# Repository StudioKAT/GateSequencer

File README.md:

# Gate Sequencer

## 概要 / Overview

**Gate Sequencer** は、トグルスイッチ式の多機能ゲートシーケンサーです。   
・独立した2つのクロックで動く **8 Stepシーケンサー x2**  
・パフォーマンス機能を備えた **16 Stepシーケンサー**  
・可変長・経路変更可能な **シフトレジスタ (Turing Machine)**  
の3つの機能を備え、スイッチ一つで切り替えて使用できます。

**Gate Sequencer** is a multi-functional gate sequencer equipped with toggle switches. It features three distinct functions that can be switched via a single mode switch:
* **8-Step Sequencer x2** running on independent clocks.
* **16-Step Sequencer** with performance features.
* **Shift Register (Turing Machine)** with variable length and routing capabilities. 

## 仕様 / Spec
- Format: Eurorack
- Function: Gate Sequencer
- Current needs: +12V: 50mA, -12V: 0mA
- Width: 14 HP
- Depth: 25mm (including power connector)

## 販売 / Sales

StudioKATオフィシャルショップで販売しています。(日本国内限定)  
https://www.studiokat.jp/items/164466252

## ライセンス / License

この作品は [Creative Commons 表示 - 継承 4.0 国際 (CC BY-SA 4.0)](https://creativecommons.org/licenses/by-sa/4.0/deed.ja) の下でライセンスされています。  
This work is licensed under the [Creative Commons Attribution-ShareAlike 4.0 International License](https://creativecommons.org/licenses/by-sa/4.0/).

## クレジット / Credits

- Designed by : StudioKAT
- Website : https://www.studiokat.jp/
- GitHub : https://github.com/StudioKAT
- X(Twitter) : https://x.com/StudioKAT_synth
- Instagram : https://www.instagram.com/studiokat_modular/

## 更新履歴 / Changelog

- `2026-10-29`：v2.0 リリース
- `2025-11-22`：v1.0 リリース

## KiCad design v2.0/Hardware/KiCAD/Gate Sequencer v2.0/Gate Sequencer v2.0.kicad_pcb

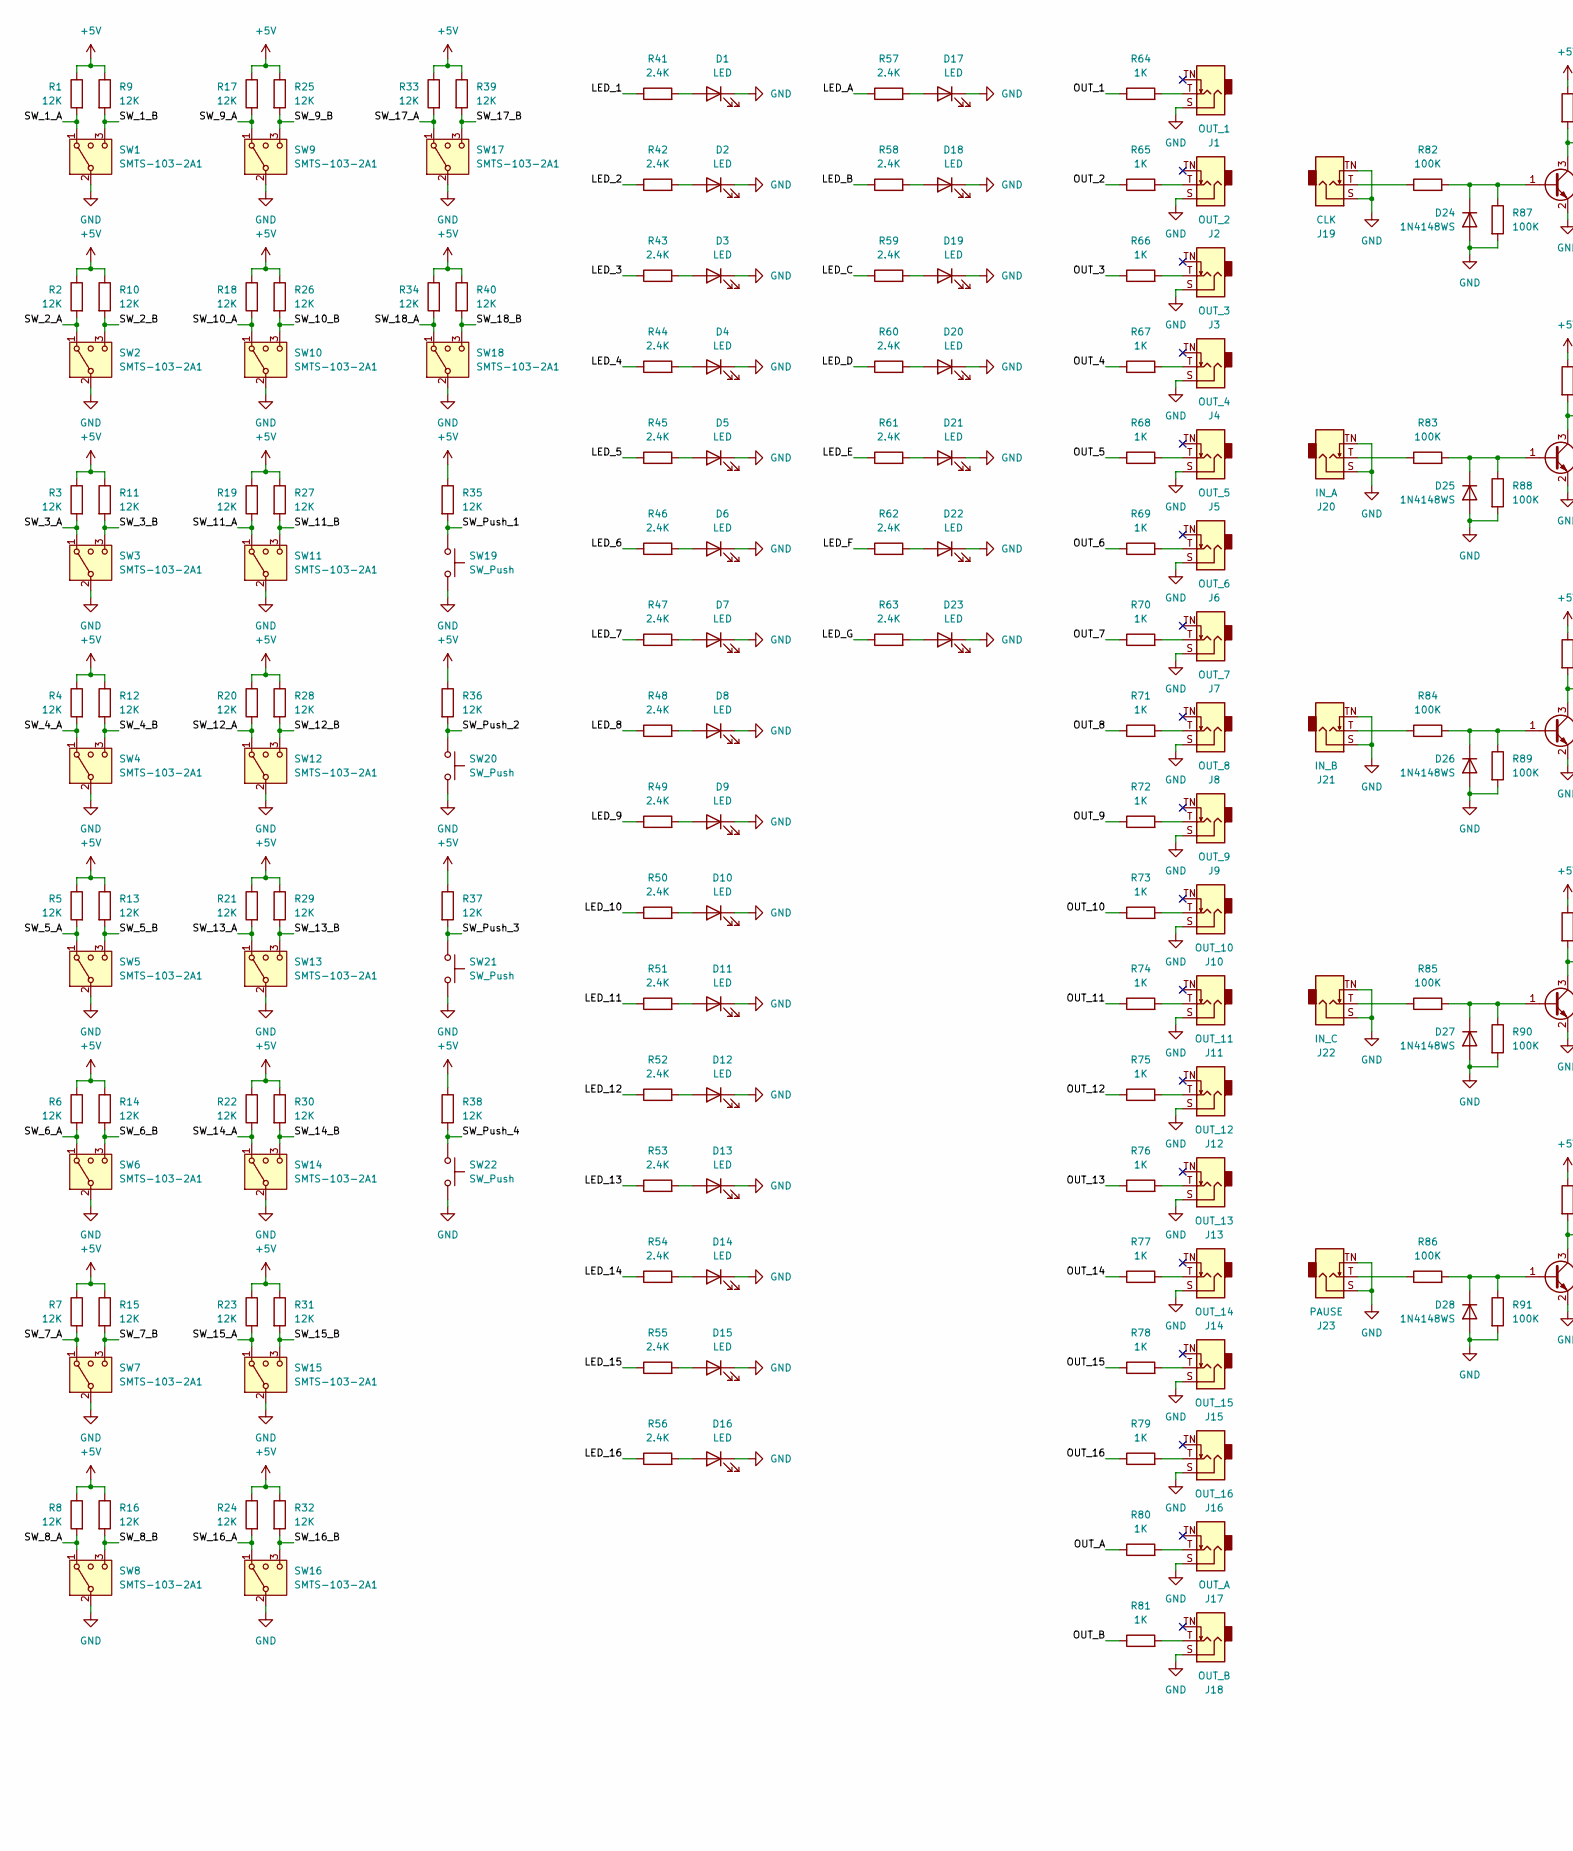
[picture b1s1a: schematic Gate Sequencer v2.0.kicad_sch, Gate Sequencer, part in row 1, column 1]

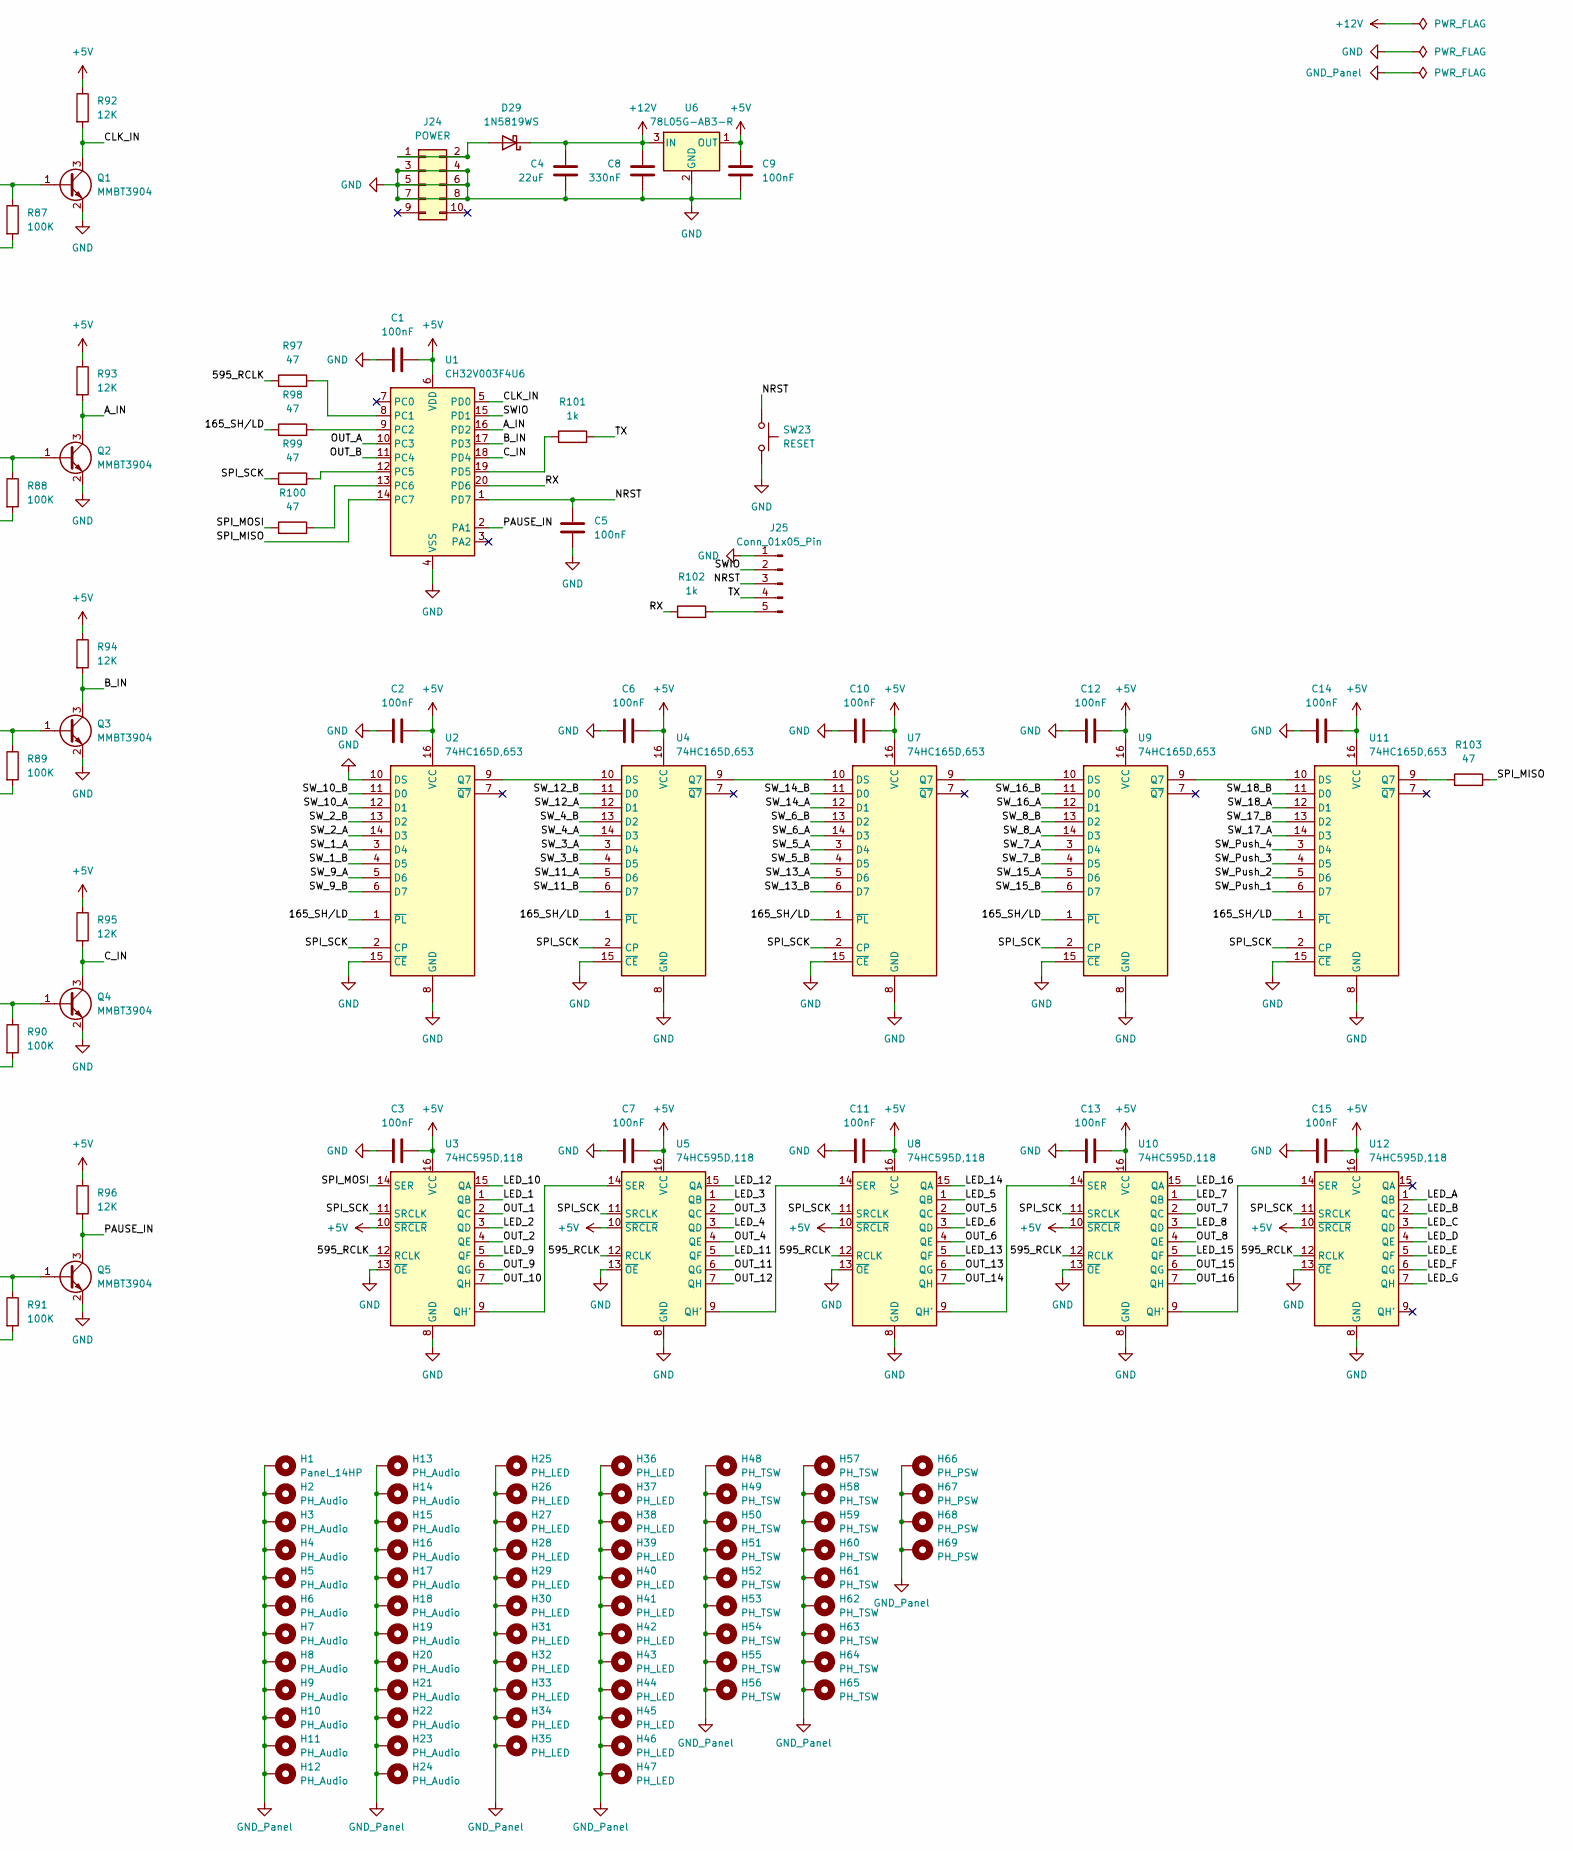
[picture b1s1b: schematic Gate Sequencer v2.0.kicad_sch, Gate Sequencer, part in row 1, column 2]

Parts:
C1, C2, C3, C6, C7, C10, C11, C12, C13, C14, C15: 100nF; C_0603_1608Metric; LCSC C14663
C4: 22uF; C_0805_2012Metric; LCSC C45783
C5, C9: 100nF; C_0603_1608Metric; Voltage 50V; Tolerance ±10%; MFR Part CC0603KRX7R9BB104; JLC Type Basic
C8: 330nF; C_0603_1608Metric; Voltage 25V; Tolerance ±10%; MFR Part 0603B334K250NT; LCSC C1615
D1, D2, D3, D4, D5, D6, D7, D8, D9, D10, D11, D12, D13, D14, D15, D16, D17, D18, D19, D20, D21, D22, D23: LED; LED_D3.0mm_2hp
D24, D25, D26, D27, D28: 1N4148WS; D_SOD-323; LCSC C2128
D29: 1N5819WS; D_SOD-323; LCSC C64886
H1: Panel_14HP
H2, H3, H4, H5, H6, H7, H8, H9, H10, H11, H12, H13, H14, H15, H16, H17, H18, H19, H20, H21, H22, H23, H24: PH_Audio; PH_AudioJack_3.5mm_Pad
H25, H26, H27, H28, H29, H30, H31, H32, H33, H34, H35, H36, H37, H38, H39, H40, H41, H42, H43, H44, H45, H46, H47: PH_LED; PH_LED_3.0mm_Pad
H48, H49, H50, H51, H52, H53, H54, H55, H56, H57, H58, H59, H60, H61, H62, H63, H64, H65: PH_TSW; PH_TactileSwitch_5.5mm_Pad
H66, H67, H68, H69: PH_PSW; PH_ToggleSwitch_5.1mm_Pad
J1: OUT_1; AudioJack_PJ301M-12
J2: OUT_2; AudioJack_PJ301M-12
J3: OUT_3; AudioJack_PJ301M-12
J4: OUT_4; AudioJack_PJ301M-12
J5: OUT_5; AudioJack_PJ301M-12
J6: OUT_6; AudioJack_PJ301M-12
J7: OUT_7; AudioJack_PJ301M-12
J8: OUT_8; AudioJack_PJ301M-12
J9: OUT_9; AudioJack_PJ301M-12
J10: OUT_10; AudioJack_PJ301M-12
J11: OUT_11; AudioJack_PJ301M-12
J12: OUT_12; AudioJack_PJ301M-12
J13: OUT_13; AudioJack_PJ301M-12
J14: OUT_14; AudioJack_PJ301M-12
J15: OUT_15; AudioJack_PJ301M-12
J16: OUT_16; AudioJack_PJ301M-12
J17: OUT_A; AudioJack_PJ301M-12
J18: OUT_B; AudioJack_PJ301M-12
J19: CLK; AudioJack_PJ301M-12
J20: IN_A; AudioJack_PJ301M-12
J21: IN_B; AudioJack_PJ301M-12
J22: IN_C; AudioJack_PJ301M-12
J23: PAUSE; AudioJack_PJ301M-12
J24: POWER; PinHeader_2x05_2.54mm_Europower
J25: Conn_01x05_Pin; PinHeader_1x05_P2.54mm_Vertical
Q1, Q2, Q3, Q4, Q5: MMBT3904; SOT-23; LCSC C20526
R1, R2, R3, R4, R5, R6, R7, R8, R9, R10, R11, R12, R13, R14, R15, R16, R17, R18, R19, R20, R21, R22, R23, R24, R25, R26, R27, R28, R29, R30, R31, R32, R33, R34, R35, R36, R37, R38, R39, R40, R92, R93, R94, R95, R96: 12K; R_0603_1608Metric; LCSC C22790
R41, R42, R43, R44, R45, R46, R47, R48, R49, R50, R51, R52, R53, R54, R55, R56, R57, R58, R59, R60, R61, R62, R63: 2.4K; R_0603_1608Metric; LCSC C22940
R64, R65, R66, R67, R68, R69, R70, R71, R72, R73, R74, R75, R76, R77, R78, R79, R80, R81: 1K; R_0603_1608Metric; LCSC C21190
R82, R83, R84, R85, R86, R87, R88, R89, R90, R91: 100K; R_0603_1608Metric; LCSC C25803
R97, R98, R99, R100, R103: 47; R_0603_1608Metric; Tolerance ±1%; MFR Part 0603WAF470JT5E; JLC Type Basic
R101, R102: 1k; R_0603_1608Metric; Tolerance ±1%; MFR Part 0603WAF1001T5E; JLC Type Basic
SW1, SW2, SW3, SW4, SW5, SW6, SW7, SW8, SW9, SW10, SW11, SW12, SW13, SW14, SW15, SW16, SW17, SW18: SMTS-103-2A1; ToggleSwitch_SMTS-103-2A1
SW19, SW20, SW21, SW22: SW_Push; SW_PUSH_6mm_H13mm
SW23: RESET; SW_Push_TS-1088-AR02016; LCSC C720477
U1: CH32V003F4U6; QFN-20-1EP_3x3mm_P0.4mm_EP1.65x1.65mm; LCSC C5299908
U2, U4, U7, U9, U11: 74HC165D,653; SOIC-16_3.9x9.9mm_P1.27mm; LCSC C5613
U3, U5, U8, U10, U12: 74HC595D,118; SOIC-16_3.9x9.9mm_P1.27mm; LCSC C5947
U6: 78L05G-AB3-R; SOT-89-3; MFR Part 78L05G-AB3-R; JLC Type Basic

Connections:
+5V: C1.2, C2.2, C3.2, C6.2, C7.2, C9.1, C10.2, C11.2, C12.2, C13.2, C14.2, C15.2, R1.1, R2.1, R3.1, R4.1, R5.1, R6.1, R7.1, R8.1, R9.1, R10.1, R11.1, R12.1, R13.1, R14.1, R15.1, R16.1, R17.1, R18.1, R19.1, R20.1, R21.1, R22.1, R23.1, R24.1, R25.1, R26.1, R27.1, R28.1, R29.1, R30.1, R31.1, R32.1, R33.1, R34.1, R35.1, R36.1, R37.1, R38.1, R39.1, R40.1, R92.1, R93.1, R94.1, R95.1, R96.1, U1.6 (VDD), U2.16 (VCC), U3.10 (~SRCLR), U3.16 (VCC), U4.16 (VCC), U5.10 (~SRCLR), U5.16 (VCC), U6.1 (OUT), U7.16 (VCC), U8.10 (~SRCLR), U8.16 (VCC), U9.16 (VCC), U10.10 (~SRCLR), U10.16 (VCC), U11.16 (VCC), U12.10 (~SRCLR), U12.16 (VCC)
+12V: C4.1, C8.1, D29.1 (K), U6.3 (IN)
/165_SH/LD: R98.1, U2.1 (~PL), U4.1 (~PL), U7.1 (~PL), U9.1 (~PL), U11.1 (~PL)
/595_RCLK: R97.1, U3.12 (RCLK), U5.12 (RCLK), U8.12 (RCLK), U10.12 (RCLK), U12.12 (RCLK)
/A_IN: Q2.3 (C), R93.2, U1.16 (PD2)
/B_IN: Q3.3 (C), R94.2, U1.17 (PD3)
/CLK_IN: Q1.3 (C), R92.2, U1.5 (PD0)
/C_IN: Q4.3 (C), R95.2, U1.18 (PD4)
/LED_1: R41.1, U3.1 (QB)
/LED_2: R42.1, U3.3 (QD)
/LED_3: R43.1, U5.1 (QB)
/LED_4: R44.1, U5.3 (QD)
/LED_5: R45.1, U8.1 (QB)
/LED_6: R46.1, U8.3 (QD)
/LED_7: R47.1, U10.1 (QB)
/LED_8: R48.1, U10.3 (QD)
/LED_9: R49.1, U3.5 (QF)
/LED_10: R50.1, U3.15 (QA)
/LED_11: R51.1, U5.5 (QF)
/LED_12: R52.1, U5.15 (QA)
/LED_13: R53.1, U8.5 (QF)
/LED_14: R54.1, U8.15 (QA)
/LED_15: R55.1, U10.5 (QF)
/LED_16: R56.1, U10.15 (QA)
/LED_A: R57.1, U12.1 (QB)
/LED_B: R58.1, U12.2 (QC)
/LED_C: R59.1, U12.3 (QD)
/LED_D: R60.1, U12.4 (QE)
/LED_E: R61.1, U12.5 (QF)
/LED_F: R62.1, U12.6 (QG)
/LED_G: R63.1, U12.7 (QH)
/NRST: C5.1, J25.3, SW23.1, U1.1 (PD7)
/OUT_1: R64.1, U3.2 (QC)
/OUT_2: R65.1, U3.4 (QE)
/OUT_3: R66.1, U5.2 (QC)
/OUT_4: R67.1, U5.4 (QE)
/OUT_5: R68.1, U8.2 (QC)
/OUT_6: R69.1, U8.4 (QE)
/OUT_7: R70.1, U10.2 (QC)
/OUT_8: R71.1, U10.4 (QE)
/OUT_9: R72.1, U3.6 (QG)
/OUT_10: R73.1, U3.7 (QH)
/OUT_11: R74.1, U5.6 (QG)
/OUT_12: R75.1, U5.7 (QH)
/OUT_13: R76.1, U8.6 (QG)
/OUT_14: R77.1, U8.7 (QH)
/OUT_15: R78.1, U10.6 (QG)
/OUT_16: R79.1, U10.7 (QH)
/OUT_A: R80.1, U1.10 (PC3)
/OUT_B: R81.1, U1.11 (PC4)
/PAUSE_IN: Q5.3 (C), R96.2, U1.2 (PA1)
/RX: R102.1, U1.20 (PD6)
/SPI_MISO: R103.2, U1.14 (PC7)
/SPI_MOSI: R100.1, U3.14 (SER)
/SPI_SCK: R99.1, U2.2 (CP), U3.11 (SRCLK), U4.2 (CP), U5.11 (SRCLK), U7.2 (CP), U8.11 (SRCLK), U9.2 (CP), U10.11 (SRCLK), U11.2 (CP), U12.11 (SRCLK)
/SWIO: J25.2, U1.15 (PD1)
/SW_1_A: R1.2, SW1.1, U2.3 (D4)
/SW_1_B: R9.2, SW1.3 (4), U2.4 (D5)
/SW_2_A: R2.2, SW2.1, U2.14 (D3)
/SW_2_B: R10.2, SW2.3 (4), U2.13 (D2)
/SW_3_A: R3.2, SW3.1, U4.3 (D4)
/SW_3_B: R11.2, SW3.3 (4), U4.4 (D5)
/SW_4_A: R4.2, SW4.1, U4.14 (D3)
/SW_4_B: R12.2, SW4.3 (4), U4.13 (D2)
/SW_5_A: R5.2, SW5.1, U7.3 (D4)
/SW_5_B: R13.2, SW5.3 (4), U7.4 (D5)
/SW_6_A: R6.2, SW6.1, U7.14 (D3)
/SW_6_B: R14.2, SW6.3 (4), U7.13 (D2)
/SW_7_A: R7.2, SW7.1, U9.3 (D4)
/SW_7_B: R15.2, SW7.3 (4), U9.4 (D5)
/SW_8_A: R8.2, SW8.1, U9.14 (D3)
/SW_8_B: R16.2, SW8.3 (4), U9.13 (D2)
/SW_9_A: R17.2, SW9.1, U2.5 (D6)
/SW_9_B: R25.2, SW9.3 (4), U2.6 (D7)
/SW_10_A: R18.2, SW10.1, U2.12 (D1)
/SW_10_B: R26.2, SW10.3 (4), U2.11 (D0)
/SW_11_A: R19.2, SW11.1, U4.5 (D6)
/SW_11_B: R27.2, SW11.3 (4), U4.6 (D7)
/SW_12_A: R20.2, SW12.1, U4.12 (D1)
/SW_12_B: R28.2, SW12.3 (4), U4.11 (D0)
/SW_13_A: R21.2, SW13.1, U7.5 (D6)
/SW_13_B: R29.2, SW13.3 (4), U7.6 (D7)
/SW_14_A: R22.2, SW14.1, U7.12 (D1)
/SW_14_B: R30.2, SW14.3 (4), U7.11 (D0)
/SW_15_A: R23.2, SW15.1, U9.5 (D6)
/SW_15_B: R31.2, SW15.3 (4), U9.6 (D7)
/SW_16_A: R24.2, SW16.1, U9.12 (D1)
/SW_16_B: R32.2, SW16.3 (4), U9.11 (D0)
/SW_17_A: R33.2, SW17.1, U11.14 (D3)
/SW_17_B: R39.2, SW17.3 (4), U11.13 (D2)
/SW_18_A: R34.2, SW18.1, U11.12 (D1)
/SW_18_B: R40.2, SW18.3 (4), U11.11 (D0)
/SW_Push_1: R35.2, SW19.1, U11.6 (D7)
/SW_Push_2: R36.2, SW20.1, U11.5 (D6)
/SW_Push_3: R37.2, SW21.1, U11.4 (D5)
/SW_Push_4: R38.2, SW22.1, U11.3 (D4)
/TX: J25.4, R101.2
GND: C1.1, C2.1, C3.1, C4.2, C5.2, C6.1, C7.1, C8.2, C9.2, C10.1, C11.1, C12.1, C13.1, C14.1, C15.1, D1.1 (K), D2.1 (K), D3.1 (K), D4.1 (K), D5.1 (K), D6.1 (K), D7.1 (K), D8.1 (K), D9.1 (K), D10.1 (K), D11.1 (K), D12.1 (K), D13.1 (K), D14.1 (K), D15.1 (K), D16.1 (K), D17.1 (K), D18.1 (K), D19.1 (K), D20.1 (K), D21.1 (K), D22.1 (K), D23.1 (K), D24.2 (A), D25.2 (A), D26.2 (A), D27.2 (A), D28.2 (A), J1.S, J2.S, J3.S, J4.S, J5.S, J6.S, J7.S, J8.S, J9.S, J10.S, J11.S, J12.S, J13.S, J14.S, J15.S, J16.S, J17.S, J18.S, J19.S, J19.TN, J20.S, J20.TN, J21.S, J21.TN, J22.S, J22.TN, J23.S, J23.TN, J24.3, J24.4, J24.5, J24.6, J24.7, J24.8, J25.1, Q1.2 (E), Q2.2 (E), Q3.2 (E), Q4.2 (E), Q5.2 (E), R87.2, R88.2, R89.2, R90.2, R91.2, SW1.2 (3), SW2.2 (3), SW3.2 (3), SW4.2 (3), SW5.2 (3), SW6.2 (3), SW7.2 (3), SW8.2 (3), SW9.2 (3), SW10.2 (3), SW11.2 (3), SW12.2 (3), SW13.2 (3), SW14.2 (3), SW15.2 (3), SW16.2 (3), SW17.2 (3), SW18.2 (3), SW19.2, SW20.2, SW21.2, SW22.2, SW23.2, U1.4 (VSS), U1.21 (VSS), U2.8 (GND), U2.10 (DS), U2.15 (~CE), U3.8 (GND), U3.13 (~OE), U4.8 (GND), U4.15 (~CE), U5.8 (GND), U5.13 (~OE), U6.2 (GND), U7.8 (GND), U7.15 (~CE), U8.8 (GND), U8.13 (~OE), U9.8 (GND), U9.15 (~CE), U10.8 (GND), U10.13 (~OE), U11.8 (GND), U11.15 (~CE), U12.8 (GND), U12.13 (~OE)
GND_Panel: H1.1 (1_1), H2.1 (1_1), H3.1 (1_1), H4.1 (1_1), H5.1 (1_1), H6.1 (1_1), H7.1 (1_1), H8.1 (1_1), H9.1 (1_1), H10.1 (1_1), H11.1 (1_1), H12.1 (1_1), H13.1 (1_1), H14.1 (1_1), H15.1 (1_1), H16.1 (1_1), H17.1 (1_1), H18.1 (1_1), H19.1 (1_1), H20.1 (1_1), H21.1 (1_1), H22.1 (1_1), H23.1 (1_1), H24.1 (1_1), H25.1 (1_1), H26.1 (1_1), H27.1 (1_1), H28.1 (1_1), H29.1 (1_1), H30.1 (1_1), H31.1 (1_1), H32.1 (1_1), H33.1 (1_1), H34.1 (1_1), H35.1 (1_1), H36.1 (1_1), H37.1 (1_1), H38.1 (1_1), H39.1 (1_1), H40.1 (1_1), H41.1 (1_1), H42.1 (1_1), H43.1 (1_1), H44.1 (1_1), H45.1 (1_1), H46.1 (1_1), H47.1 (1_1), H48.1 (1_1), H49.1 (1_1), H50.1 (1_1), H51.1 (1_1), H52.1 (1_1), H53.1 (1_1), H54.1 (1_1), H55.1 (1_1), H56.1 (1_1), H57.1 (1_1), H58.1 (1_1), H59.1 (1_1), H60.1 (1_1), H61.1 (1_1), H62.1 (1_1), H63.1 (1_1), H64.1 (1_1), H65.1 (1_1), H66.1 (1_1), H67.1 (1_1), H68.1 (1_1), H69.1 (1_1)
unnamed: D1.2 (A), R41.2
unnamed: D2.2 (A), R42.2
unnamed: D3.2 (A), R43.2
unnamed: D4.2 (A), R44.2
unnamed: D5.2 (A), R45.2
unnamed: D6.2 (A), R46.2
unnamed: D7.2 (A), R47.2
unnamed: D8.2 (A), R48.2
unnamed: D9.2 (A), R49.2
unnamed: D10.2 (A), R50.2
unnamed: D11.2 (A), R51.2
unnamed: D12.2 (A), R52.2
unnamed: D13.2 (A), R53.2
unnamed: D14.2 (A), R54.2
unnamed: D15.2 (A), R55.2
unnamed: D16.2 (A), R56.2
unnamed: D17.2 (A), R57.2
unnamed: D18.2 (A), R58.2
unnamed: D19.2 (A), R59.2
unnamed: D20.2 (A), R60.2
unnamed: D21.2 (A), R61.2
unnamed: D22.2 (A), R62.2
unnamed: D23.2 (A), R63.2
unnamed: D24.1 (K), Q1.1 (B), R82.2, R87.1
unnamed: D25.1 (K), Q2.1 (B), R83.2, R88.1
unnamed: D26.1 (K), Q3.1 (B), R84.2, R89.1
unnamed: D27.1 (K), Q4.1 (B), R85.2, R90.1
unnamed: D28.1 (K), Q5.1 (B), R86.2, R91.1
unnamed: D29.2 (A), J24.1, J24.2
unnamed: J1.T, R64.2
unnamed: J2.T, R65.2
unnamed: J3.T, R66.2
unnamed: J4.T, R67.2
unnamed: J5.T, R68.2
unnamed: J6.T, R69.2
unnamed: J7.T, R70.2
unnamed: J8.T, R71.2
unnamed: J9.T, R72.2
unnamed: J10.T, R73.2
unnamed: J11.T, R74.2
unnamed: J12.T, R75.2
unnamed: J13.T, R76.2
unnamed: J14.T, R77.2
unnamed: J15.T, R78.2
unnamed: J16.T, R79.2
unnamed: J17.T, R80.2
unnamed: J18.T, R81.2
unnamed: J19.T, R82.1
unnamed: J20.T, R83.1
unnamed: J21.T, R84.1
unnamed: J22.T, R85.1
unnamed: J23.T, R86.1
unnamed: J25.5, R102.2
unnamed: R97.2, U1.8 (PC1)
unnamed: R98.2, U1.9 (PC2)
unnamed: R99.2, U1.12 (PC5)
unnamed: R100.2, U1.13 (PC6)
unnamed: R101.1, U1.19 (PD5)
unnamed: U2.9 (Q7), U4.10 (DS)
unnamed: U3.9 (QH'), U5.14 (SER)
unnamed: U4.9 (Q7), U7.10 (DS)
unnamed: U5.9 (QH'), U8.14 (SER)
unnamed: U7.9 (Q7), U9.10 (DS)
unnamed: U10.9 (QH'), U12.14 (SER)
unnamed: U8.9 (QH'), U10.14 (SER)
unnamed: U9.9 (Q7), U11.10 (DS)
unnamed: R103.1, U11.9 (Q7)

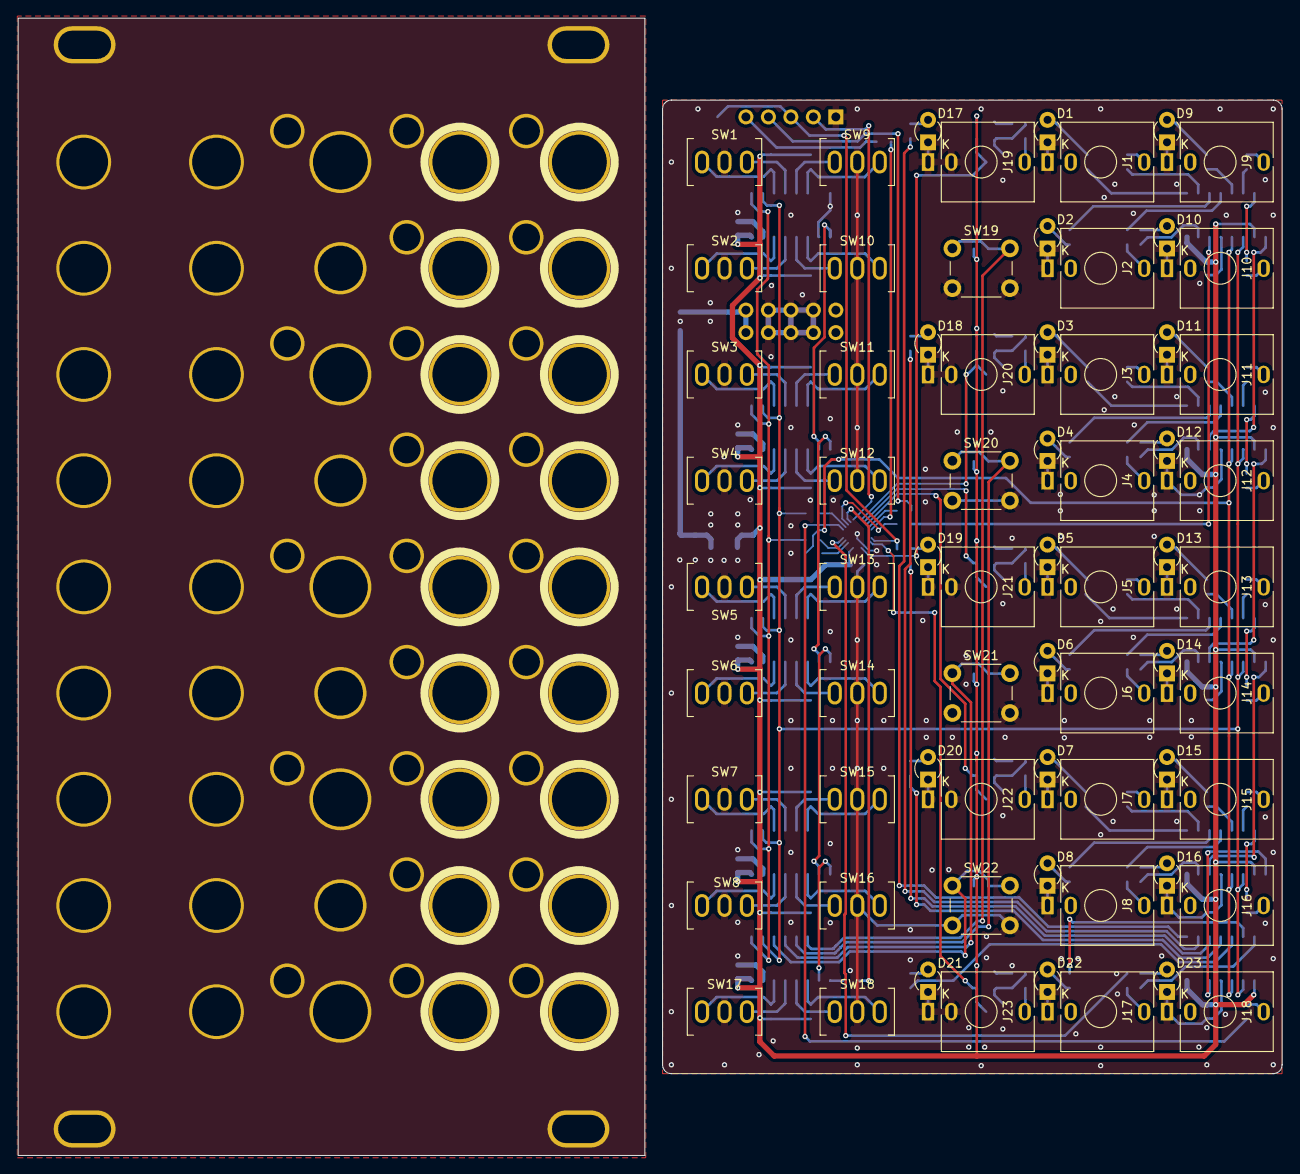
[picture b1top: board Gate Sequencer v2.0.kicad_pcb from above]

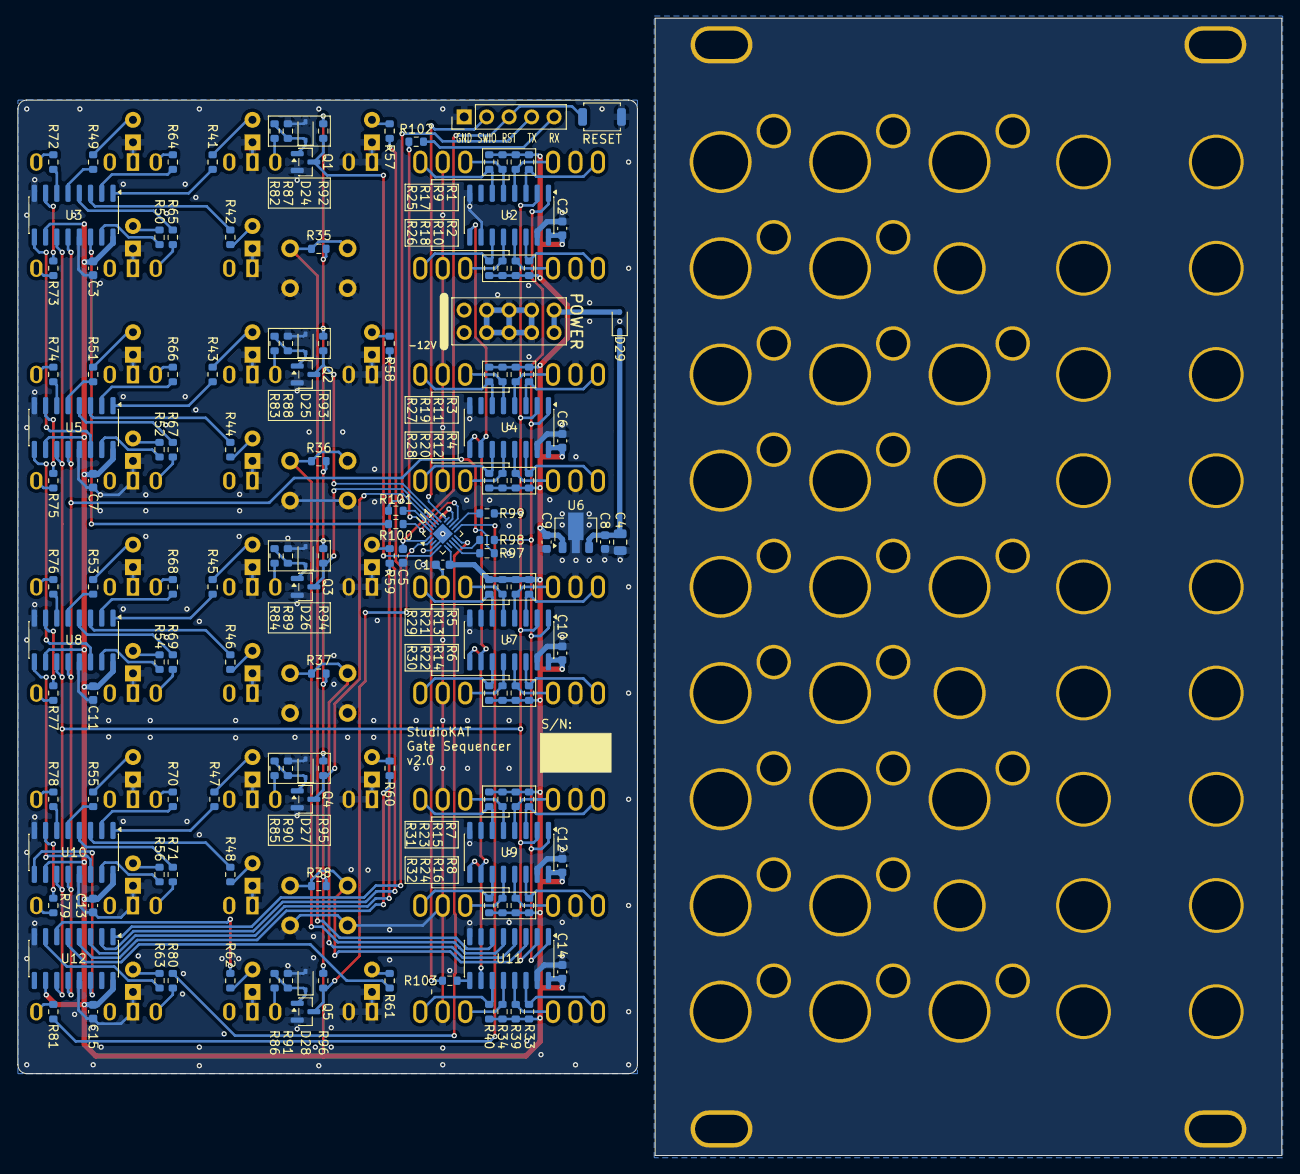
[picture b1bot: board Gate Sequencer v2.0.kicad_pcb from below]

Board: 2 copper layers, 142.8 x 128.5 mm, 281 parts (144 on the bottom side), 166 nets.
